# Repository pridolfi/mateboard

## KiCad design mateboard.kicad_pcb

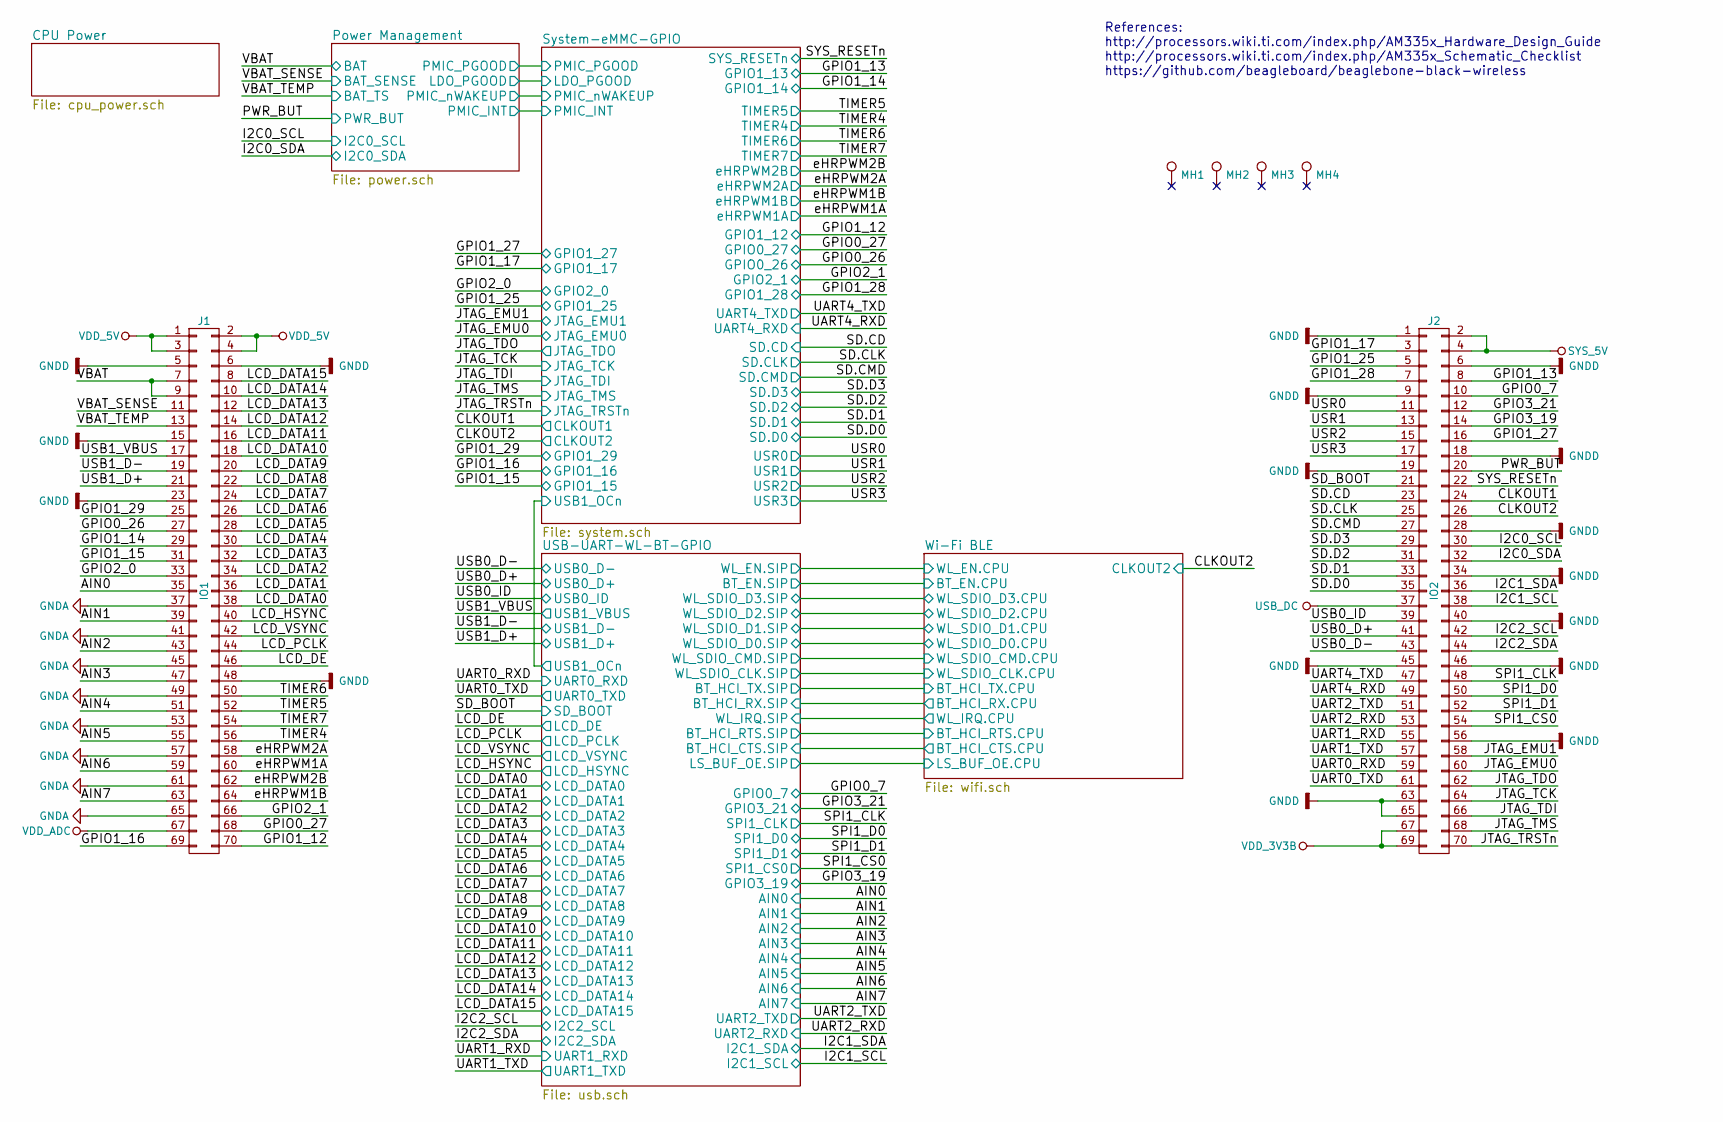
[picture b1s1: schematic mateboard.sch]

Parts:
J1: IO1; DF40C-70DP-0.4V_51_
J2: IO2; DF40C-70DP-0.4V_51_
MH1, MH2, MH3, MH4: Mounting hole; MountingHole_3.2mm_M3

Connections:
/AIN0: J1.35; also elsewhere on the board
/AIN1: J1.39; also elsewhere on the board
/AIN2: J1.43; also elsewhere on the board
/AIN3: J1.47; also elsewhere on the board
/AIN4: J1.51; also elsewhere on the board
/AIN5: J1.55; also elsewhere on the board
/AIN6: J1.59; also elsewhere on the board
/AIN7: J1.63; also elsewhere on the board
/CLKOUT1: J2.24; also elsewhere on the board
/CLKOUT2: J2.26; also elsewhere on the board
/GPIO0_7: J2.10; also elsewhere on the board
/GPIO0_26: J1.27; also elsewhere on the board
/GPIO0_27: J1.68; also elsewhere on the board
/GPIO1_12: J1.70; also elsewhere on the board
/GPIO1_13: J2.8; also elsewhere on the board
/GPIO1_14: J1.29; also elsewhere on the board
/GPIO1_15: J1.31; also elsewhere on the board
/GPIO1_16: J1.69; also elsewhere on the board
/GPIO1_17: J2.3; also elsewhere on the board
/GPIO1_25: J2.5; also elsewhere on the board
/GPIO1_27: J2.16; also elsewhere on the board
/GPIO1_28: J2.7; also elsewhere on the board
/GPIO1_29: J1.25; also elsewhere on the board
/GPIO2_0: J1.33; also elsewhere on the board
/GPIO2_1: J1.66; also elsewhere on the board
/GPIO3_19: J2.14; also elsewhere on the board
/GPIO3_21: J2.12; also elsewhere on the board
/I2C0_SCL: J2.30; also elsewhere on the board
/I2C0_SDA: J2.32; also elsewhere on the board
/I2C1_SCL: J2.38; also elsewhere on the board
/I2C1_SDA: J2.36; also elsewhere on the board
/I2C2_SCL: J2.42; also elsewhere on the board
/I2C2_SDA: J2.44; also elsewhere on the board
/JTAG_EMU0: J2.60; also elsewhere on the board
/JTAG_EMU1: J2.58; also elsewhere on the board
/JTAG_TCK: J2.64; also elsewhere on the board
/JTAG_TDI: J2.66; also elsewhere on the board
/JTAG_TDO: J2.62; also elsewhere on the board
/JTAG_TMS: J2.68; also elsewhere on the board
/JTAG_TRSTn: J2.70; also elsewhere on the board
/LCD_DATA0: J1.38; also elsewhere on the board
/LCD_DATA1: J1.36; also elsewhere on the board
/LCD_DATA2: J1.34; also elsewhere on the board
/LCD_DATA3: J1.32; also elsewhere on the board
/LCD_DATA4: J1.30; also elsewhere on the board
/LCD_DATA5: J1.28; also elsewhere on the board
/LCD_DATA6: J1.26; also elsewhere on the board
/LCD_DATA7: J1.24; also elsewhere on the board
/LCD_DATA8: J1.22; also elsewhere on the board
/LCD_DATA9: J1.20; also elsewhere on the board
/LCD_DATA10: J1.18; also elsewhere on the board
/LCD_DATA11: J1.16; also elsewhere on the board
/LCD_DATA12: J1.14; also elsewhere on the board
/LCD_DATA13: J1.12; also elsewhere on the board
/LCD_DATA14: J1.10; also elsewhere on the board
/LCD_DATA15: J1.8; also elsewhere on the board
/LCD_DE: J1.46; also elsewhere on the board
/LCD_HSYNC: J1.40; also elsewhere on the board
/LCD_PCLK: J1.44; also elsewhere on the board
/LCD_VSYNC: J1.42; also elsewhere on the board
/PWR_BUT: J2.20; also elsewhere on the board
/SD.CD: J2.23; also elsewhere on the board
/SD.CLK: J2.25; also elsewhere on the board
/SD.CMD: J2.27; also elsewhere on the board
/SD.D0: J2.35; also elsewhere on the board
/SD.D1: J2.33; also elsewhere on the board
/SD.D2: J2.31; also elsewhere on the board
/SD.D3: J2.29; also elsewhere on the board
/SD_BOOT: J2.21; also elsewhere on the board
/SPI1_CLK: J2.48; also elsewhere on the board
/SPI1_CS0: J2.54; also elsewhere on the board
/SPI1_D0: J2.50; also elsewhere on the board
/SPI1_D1: J2.52; also elsewhere on the board
/SYS_RESETn: J2.22; also elsewhere on the board
/TIMER4: J1.56; also elsewhere on the board
/TIMER5: J1.52; also elsewhere on the board
/TIMER6: J1.50; also elsewhere on the board
/TIMER7: J1.54; also elsewhere on the board
/UART0_RXD: J2.59; also elsewhere on the board
/UART0_TXD: J2.61; also elsewhere on the board
/UART1_RXD: J2.55; also elsewhere on the board
/UART1_TXD: J2.57; also elsewhere on the board
/UART2_RXD: J2.53; also elsewhere on the board
/UART2_TXD: J2.51; also elsewhere on the board
/UART4_RXD: J2.49; also elsewhere on the board
/UART4_TXD: J2.47; also elsewhere on the board
/USB0_D+: J2.41; also elsewhere on the board
/USB0_D-: J2.43; also elsewhere on the board
/USB0_ID: J2.39; also elsewhere on the board
/USB1_D+: J1.21; also elsewhere on the board
/USB1_D-: J1.19; also elsewhere on the board
/USB1_VBUS: J1.17; also elsewhere on the board
/USR0: J2.11; also elsewhere on the board
/USR1: J2.13; also elsewhere on the board
/USR2: J2.15; also elsewhere on the board
/USR3: J2.17; also elsewhere on the board
/VBAT: J1.7, J1.9; also elsewhere on the board
/VBAT_SENSE: J1.11; also elsewhere on the board
/VBAT_TEMP: J1.13; also elsewhere on the board
/eHRPWM1A: J1.60; also elsewhere on the board
/eHRPWM1B: J1.64; also elsewhere on the board
/eHRPWM2A: J1.58; also elsewhere on the board
/eHRPWM2B: J1.62; also elsewhere on the board
GNDA: J1.37, J1.41, J1.45, J1.49, J1.53, J1.57, J1.61, J1.65; also elsewhere on the board
GNDD: J1.5, J1.6, J1.15, J1.23, J1.48, J2.1, J2.6, J2.9, J2.18, J2.19, J2.28, J2.34, J2.40, J2.45, J2.46, J2.56, J2.63, J2.65; also elsewhere on the board
SYS_5V: J2.2, J2.4; also elsewhere on the board
USB_DC: J2.37; also elsewhere on the board
VDD_3V3B: J2.67, J2.69; also elsewhere on the board
VDD_5V: J1.1, J1.2, J1.3, J1.4; also elsewhere on the board
VDD_ADC: J1.67; also elsewhere on the board

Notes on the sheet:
References: http://processors.wiki.ti.com/index.php/AM335x_Hardware_Design_Guide http://processors.wiki.ti.com/index.php/AM335x_Schematic_Checklist https://github.com/beagleboard/beaglebone-black-wireless

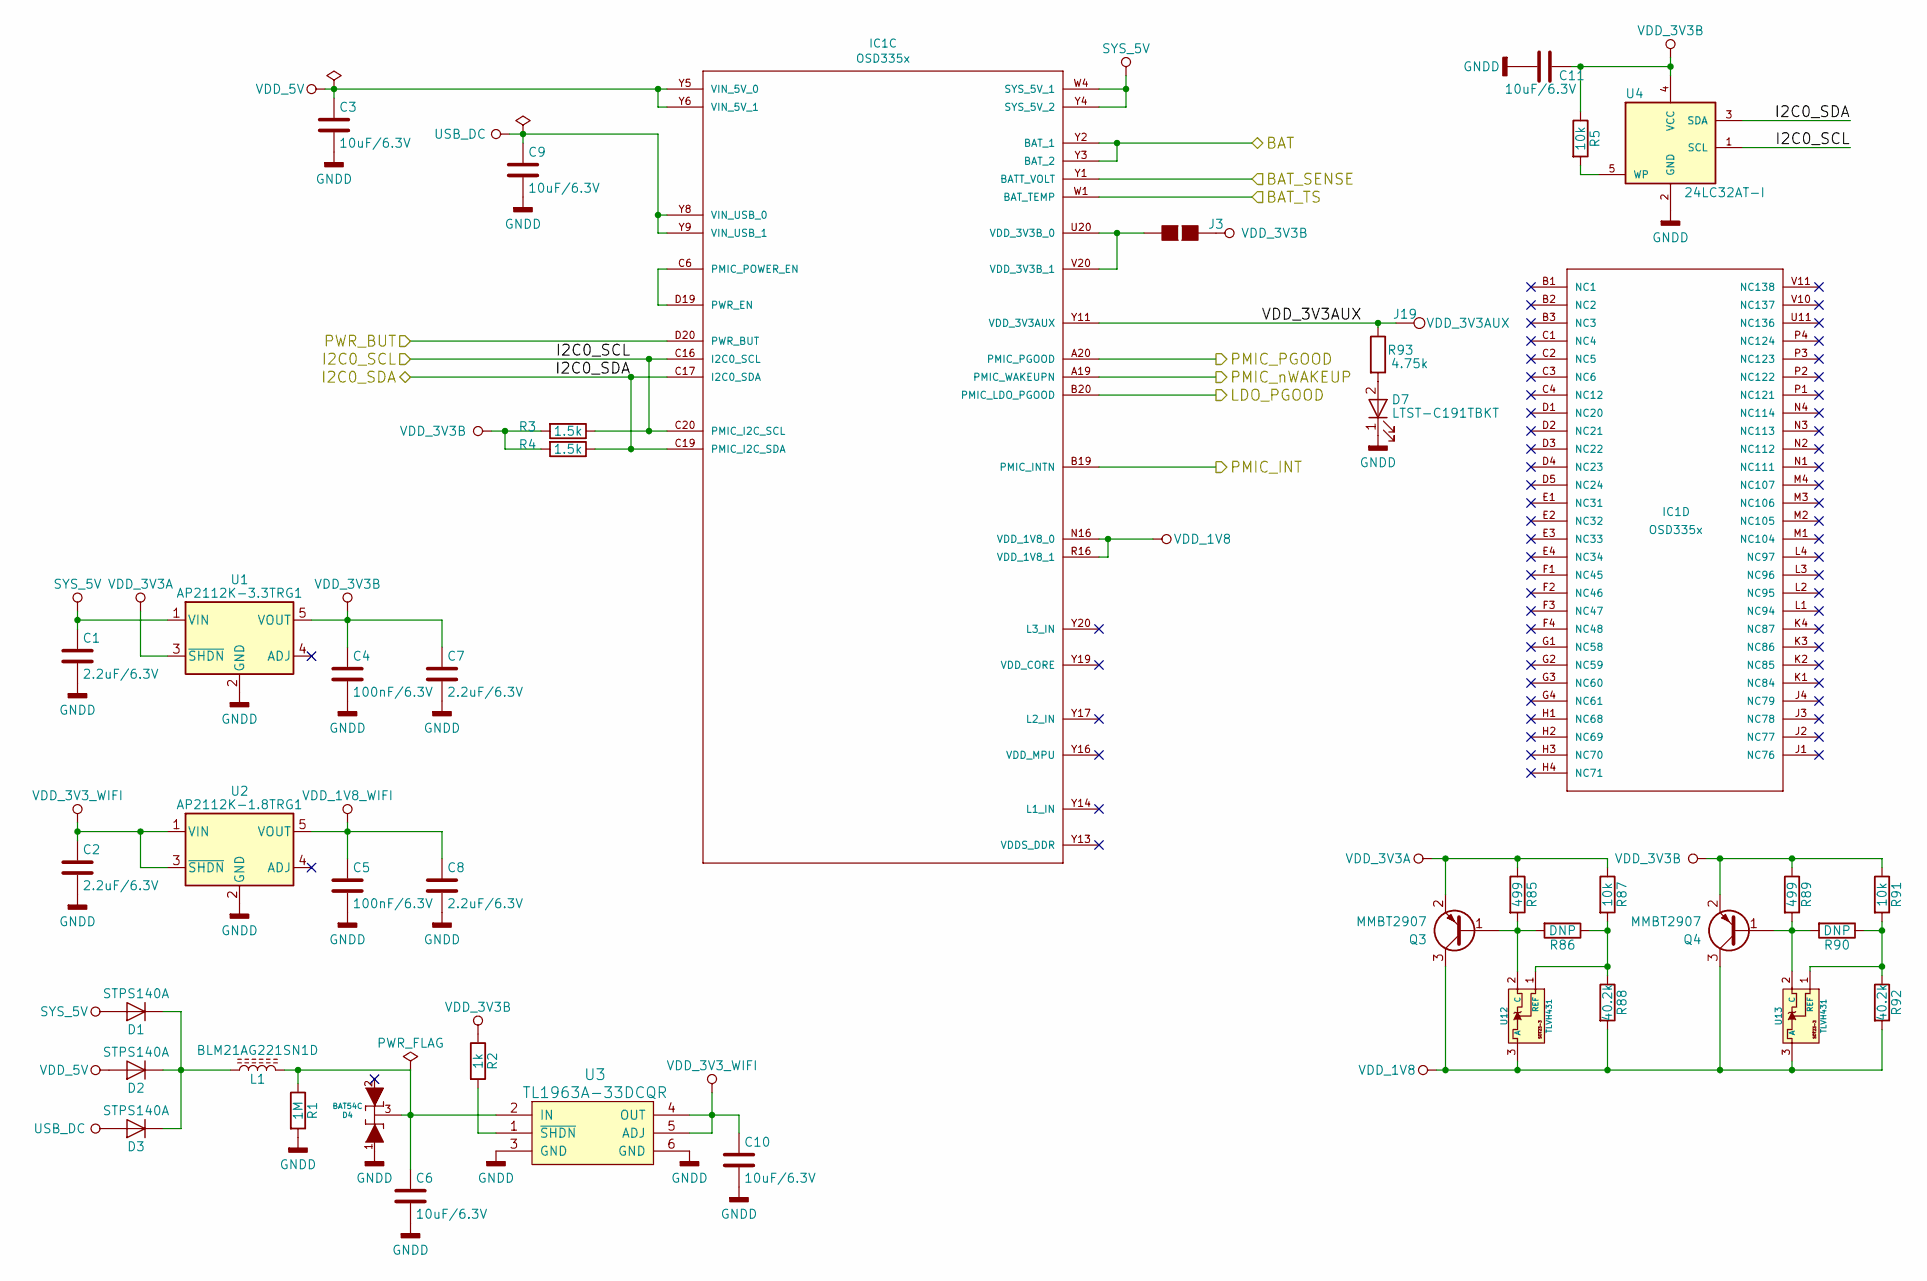
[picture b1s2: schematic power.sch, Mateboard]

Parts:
C1, C2, C7, C8: 2.2uF/6.3V; C_0603
C3, C6, C9, C10, C11: 10uF/6.3V; C_0603
C4, C5: 100nF/6.3V; C_0402
D1, D2, D3: STPS140A; D_SMA_Standard
D4: BAT54C; SOT-23
D7: LTST-C191TBKT; LED_0603
IC1: OSD335x; OSD3358-BAS-BGA400
J3: GS2
J19: VDD_3V3AUX; Measurement_Point_Round-SMD-Pad_Small
L1: BLM21AG221SN1D; R_0805
Q3, Q4: MMBT2907; SOT-23
R1: 1M; R_0402
R2: 1k; R_0402
R3, R4: 1.5k; R_0402
R5, R87, R91: 10k; R_0402
R85, R89: 499; R_0402
R86, R90: DNP; R_0402
R88, R92: 40.2k; R_0402
R93: 4.75k; R_0402
U1: AP2112K-3.3TRG1; TSOT-23-5
U2: AP2112K-1.8TRG1; TSOT-23-5
U3: TL1963A-33DCQR; SOT-223-6
U4: 24LC32AT-I; SOT-23-5
U12, U13: TLVH431; SOT-23

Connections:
/I2C0_SCL: IC1.C16 (I2C0_SCL), IC1.C20 (PMIC_I2C_SCL), R3.1, U4.1 (SCL); also elsewhere on the board
/I2C0_SDA: IC1.C17 (I2C0_SDA), IC1.C19 (PMIC_I2C_SDA), R4.1, U4.3 (SDA); also elsewhere on the board
/PWR_BUT: IC1.D20 (PWR_BUT); also elsewhere on the board
/Power Management/LDO_PGOOD: IC1.B20 (PMIC_LDO_PGOOD); also elsewhere on the board
/Power Management/PMIC_INT: IC1.B19 (PMIC_INTN); also elsewhere on the board
/Power Management/PMIC_PGOOD: IC1.A20 (PMIC_PGOOD); also elsewhere on the board
/Power Management/PMIC_nWAKEUP: IC1.A19 (PMIC_WAKEUPN); also elsewhere on the board
/Power Management/VDD_3V3AUX: IC1.Y11 (VDD_3V3AUX), J19.1, R93.1
/VBAT: IC1.Y2 (BAT_1), IC1.Y3 (BAT_2); also elsewhere on the board
/VBAT_SENSE: IC1.Y1 (BATT_VOLT); also elsewhere on the board
/VBAT_TEMP: IC1.W1 (BAT_TEMP); also elsewhere on the board
GNDD: C1.2, C2.2, C3.2, C4.2, C5.2, C6.2, C7.2, C8.2, C9.2, C10.2, C11.2, D4.1 (B), D7.1 (K), R1.2, U1.2 (GND), U2.2 (GND), U3.3 (GND), U3.6 (GND), U4.2 (GND); also elsewhere on the board
unnamed: C6.1, D4.3 (C), L1.2, R1.1, U3.2 (IN)
unnamed: D1.1 (K), D2.1 (K), D3.1 (K), L1.1
unnamed: D7.2 (A), R93.2
unnamed: IC1.C6 (PMIC_POWER_EN), IC1.D19 (PWR_EN)
unnamed: IC1.U20 (VDD_3V3B_0), IC1.V20 (VDD_3V3B_1), J3.2 (G2)
unnamed: Q3.1 (B), R85.2, R86.2, U12.2 (C)
unnamed: Q4.1 (B), R89.2, R90.2, U13.2 (C)
unnamed: R2.2, U3.1 (~SHDN)
unnamed: R5.2, U4.5 (WP)
unnamed: R86.1, R87.2, R88.1, U12.1 (REF)
unnamed: R90.1, R91.2, R92.1, U13.1 (REF)
SYS_5V: C1.1, D1.2 (A), IC1.W4 (SYS_5V_1), IC1.Y4 (SYS_5V_2), U1.1 (VIN); also elsewhere on the board
USB_DC: C9.1, D3.2 (A), IC1.Y8 (VIN_USB_0), IC1.Y9 (VIN_USB_1); also elsewhere on the board
VDD_1V8: IC1.N16 (VDD_1V8_0), IC1.R16 (VDD_1V8_1), Q3.3 (C), Q4.3 (C), R88.2, R92.2, U12.3 (A), U13.3 (A); also elsewhere on the board
VDD_1V8_WIFI: C5.1, C8.1, U2.5 (VOUT); also elsewhere on the board
VDD_3V3A: Q3.2 (E), R85.1, R87.1, U1.3 (~SHDN); also elsewhere on the board
VDD_3V3B: C4.1, C7.1, C11.1, J3.1 (G1), Q4.2 (E), R2.1, R3.2, R4.2, R5.1, R89.1, R91.1, U1.5 (VOUT), U4.4 (VCC); also elsewhere on the board
VDD_3V3_WIFI: C2.1, C10.1, U2.1 (VIN), U2.3 (~SHDN), U3.4 (OUT), U3.5 (ADJ); also elsewhere on the board
VDD_5V: C3.1, D2.2 (A), IC1.Y5 (VIN_5V_0), IC1.Y6 (VIN_5V_1); also elsewhere on the board

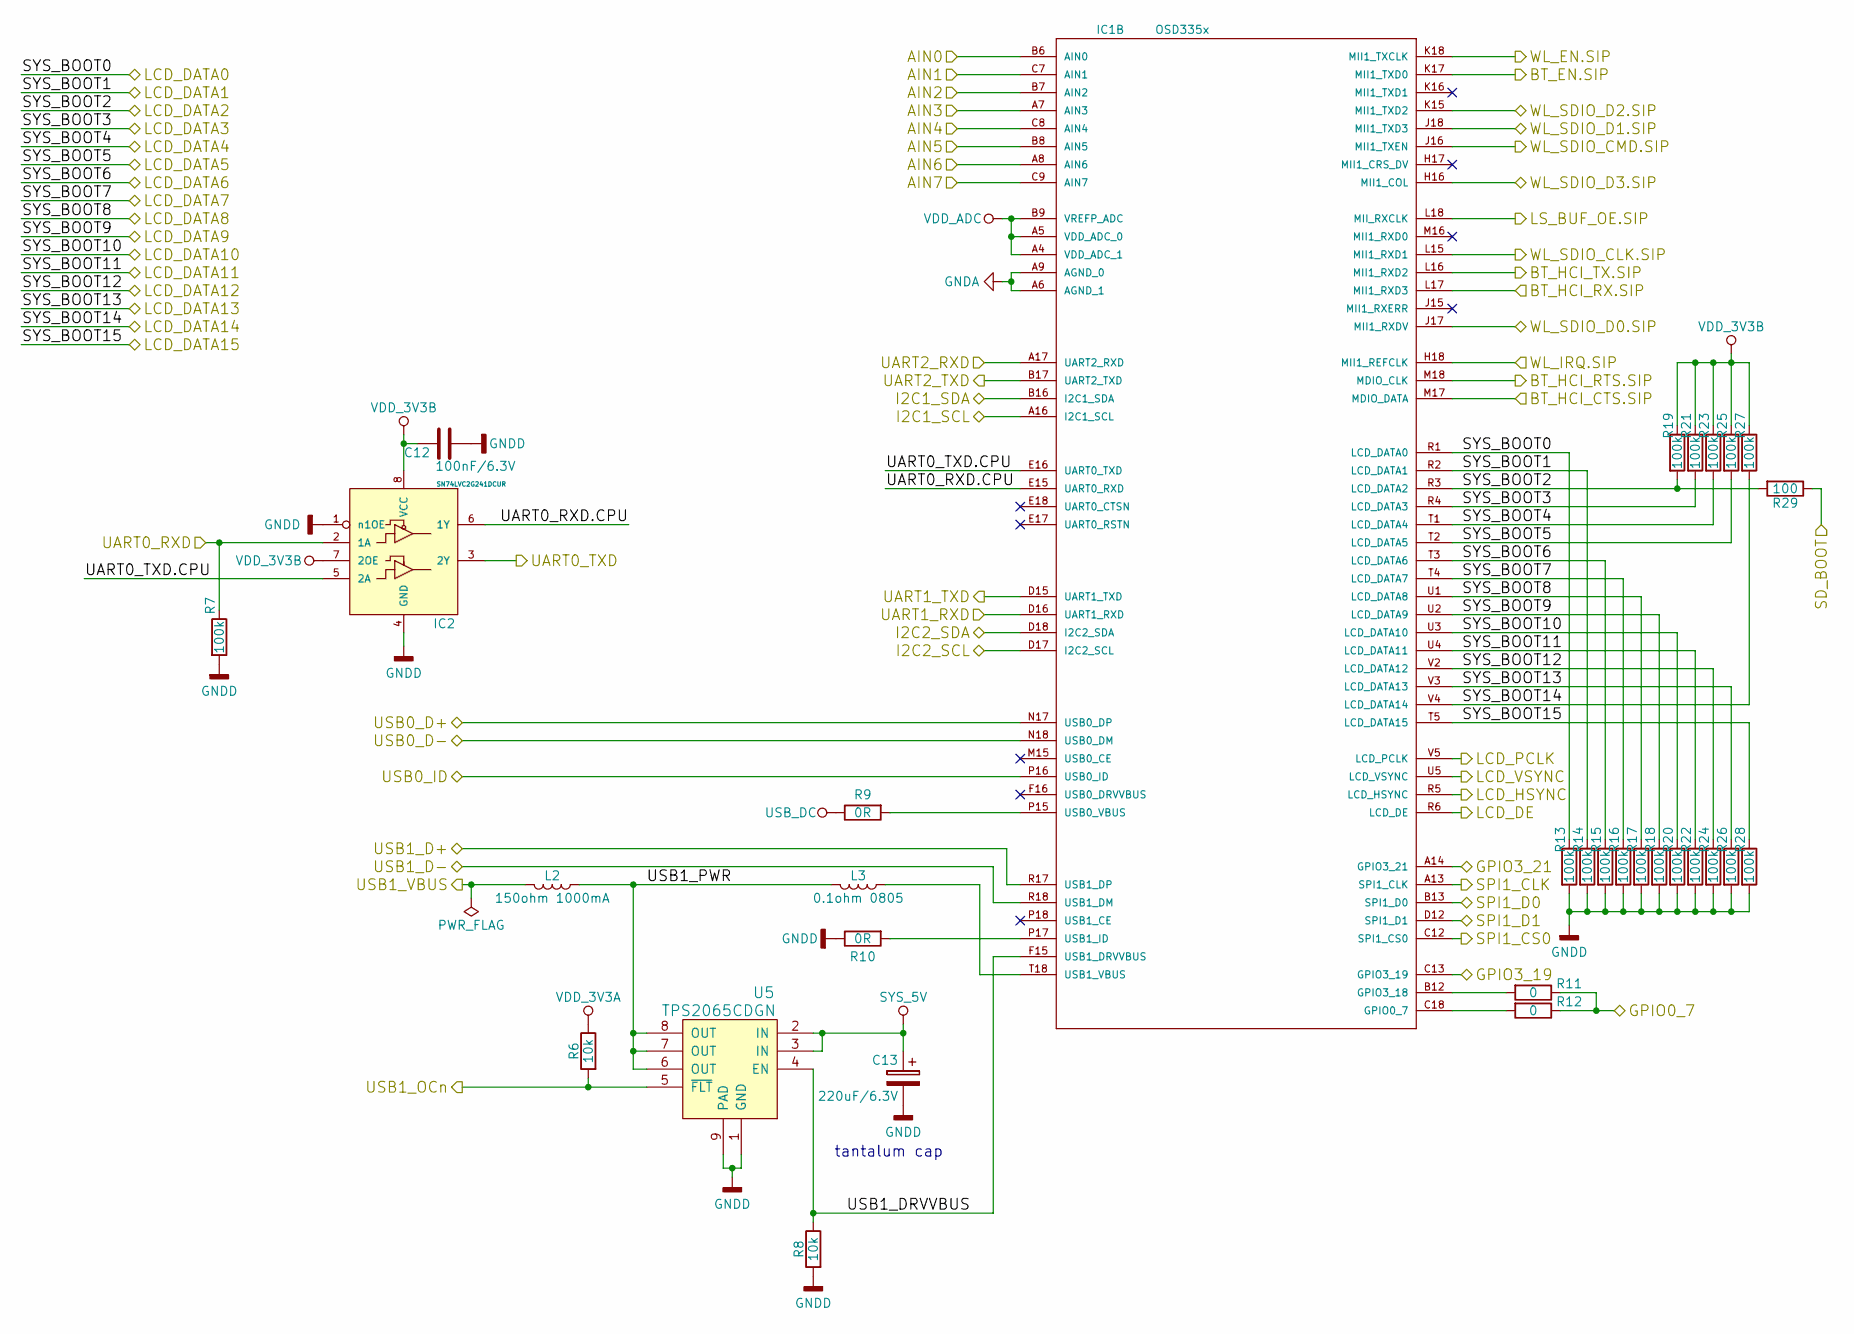
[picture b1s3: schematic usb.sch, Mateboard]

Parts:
C12: 100nF/6.3V; C_0402
C13: 220uF/6.3V; CP_Tantalum_Case-A_EIA-3216-18_Reflow
IC1: OSD335x; OSD3358-BAS-BGA400
IC2: SN74LVC2G241DCUR; VSSOP-8_2.3x2mm_Pitch0.5mm
L2: 150ohm 1000mA; R_0805
L3: 0.1ohm 0805; R_0805
R6, R8: 10k; R_0402
R7, R13, R14, R15, R16, R17, R18, R19, R20, R21, R22, R23, R24, R25, R26, R27, R28: 100k; R_0402
R9, R10: 0R; R_0402
R11, R12: 0; R_0402
R29: 100; R_0402
U5: TPS2065CDGN; MSOP-8-1EP_3x3mm_Pitch0.65mm

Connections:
/AIN0: IC1.B6 (AIN0); also elsewhere on the board
/AIN1: IC1.C7 (AIN1); also elsewhere on the board
/AIN2: IC1.B7 (AIN2); also elsewhere on the board
/AIN3: IC1.A7 (AIN3); also elsewhere on the board
/AIN4: IC1.C8 (AIN4); also elsewhere on the board
/AIN5: IC1.B8 (AIN5); also elsewhere on the board
/AIN6: IC1.A8 (AIN6); also elsewhere on the board
/AIN7: IC1.C9 (AIN7); also elsewhere on the board
/GPIO0_7: R11.1, R12.1; also elsewhere on the board
/GPIO3_19: IC1.C13 (GPIO3_19); also elsewhere on the board
/GPIO3_21: IC1.A14 (GPIO3_21); also elsewhere on the board
/I2C1_SCL: IC1.A16 (I2C1_SCL); also elsewhere on the board
/I2C1_SDA: IC1.B16 (I2C1_SDA); also elsewhere on the board
/I2C2_SCL: IC1.D17 (I2C2_SCL); also elsewhere on the board
/I2C2_SDA: IC1.D18 (I2C2_SDA); also elsewhere on the board
/LCD_DATA0: IC1.R1 (LCD_DATA0), R13.1; also elsewhere on the board
/LCD_DATA1: IC1.R2 (LCD_DATA1), R14.1; also elsewhere on the board
/LCD_DATA2: IC1.R3 (LCD_DATA2), R19.2, R29.2; also elsewhere on the board
/LCD_DATA3: IC1.R4 (LCD_DATA3), R21.2; also elsewhere on the board
/LCD_DATA4: IC1.T1 (LCD_DATA4), R23.2; also elsewhere on the board
/LCD_DATA5: IC1.T2 (LCD_DATA5), R25.2; also elsewhere on the board
/LCD_DATA6: IC1.T3 (LCD_DATA6), R15.1; also elsewhere on the board
/LCD_DATA7: IC1.T4 (LCD_DATA7), R16.1; also elsewhere on the board
/LCD_DATA8: IC1.U1 (LCD_DATA8), R17.1; also elsewhere on the board
/LCD_DATA9: IC1.U2 (LCD_DATA9), R18.1; also elsewhere on the board
/LCD_DATA10: IC1.U3 (LCD_DATA10), R20.1; also elsewhere on the board
/LCD_DATA11: IC1.U4 (LCD_DATA11), R22.1; also elsewhere on the board
/LCD_DATA12: IC1.V2 (LCD_DATA12), R24.1; also elsewhere on the board
/LCD_DATA13: IC1.V3 (LCD_DATA13), R26.1; also elsewhere on the board
/LCD_DATA14: IC1.V4 (LCD_DATA14), R27.2; also elsewhere on the board
/LCD_DATA15: IC1.T5 (LCD_DATA15), R28.1; also elsewhere on the board
/LCD_DE: IC1.R6 (LCD_DE); also elsewhere on the board
/LCD_HSYNC: IC1.R5 (LCD_HSYNC); also elsewhere on the board
/LCD_PCLK: IC1.V5 (LCD_PCLK); also elsewhere on the board
/LCD_VSYNC: IC1.U5 (LCD_VSYNC); also elsewhere on the board
/SD_BOOT: R29.1; also elsewhere on the board
/SPI1_CLK: IC1.A13 (SPI1_CLK); also elsewhere on the board
/SPI1_CS0: IC1.C12 (SPI1_CS0); also elsewhere on the board
/SPI1_D0: IC1.B13 (SPI1_D0); also elsewhere on the board
/SPI1_D1: IC1.D12 (SPI1_D1); also elsewhere on the board
/System-eMMC-GPIO/USB1_OCn: R6.2, U5.5 (~FLT); also elsewhere on the board
/UART0_RXD: IC2.2 (1A), R7.1; also elsewhere on the board
/UART0_TXD: IC2.3 (2Y); also elsewhere on the board
/UART1_RXD: IC1.D16 (UART1_RXD); also elsewhere on the board
/UART1_TXD: IC1.D15 (UART1_TXD); also elsewhere on the board
/UART2_RXD: IC1.A17 (UART2_RXD); also elsewhere on the board
/UART2_TXD: IC1.B17 (UART2_TXD); also elsewhere on the board
/USB0_D+: IC1.N17 (USB0_DP); also elsewhere on the board
/USB0_D-: IC1.N18 (USB0_DM); also elsewhere on the board
/USB0_ID: IC1.P16 (USB0_ID); also elsewhere on the board
/USB1_D+: IC1.R17 (USB1_DP); also elsewhere on the board
/USB1_D-: IC1.R18 (USB1_DM); also elsewhere on the board
/USB1_VBUS: L2.1; also elsewhere on the board
/USB-UART-WL-BT-GPIO/UART0_RXD.CPU: IC1.E15 (UART0_RXD), IC2.6 (1Y)
/USB-UART-WL-BT-GPIO/UART0_TXD.CPU: IC1.E16 (UART0_TXD), IC2.5 (2A)
/USB-UART-WL-BT-GPIO/USB1_DRVVBUS: IC1.F15 (USB1_DRVVBUS), R8.1, U5.4 (EN)
/USB-UART-WL-BT-GPIO/USB1_PWR: L2.2, L3.1, U5.6 (OUT), U5.7 (OUT), U5.8 (OUT)
/Wi-Fi BLE/BT_EN.CPU: IC1.K17 (MII1_TXD0); also elsewhere on the board
/Wi-Fi BLE/BT_HCI_CTS.CPU: IC1.M17 (MDIO_DATA); also elsewhere on the board
/Wi-Fi BLE/BT_HCI_RTS.CPU: IC1.M18 (MDIO_CLK); also elsewhere on the board
/Wi-Fi BLE/BT_HCI_RX.CPU: IC1.L17 (MII1_RXD3); also elsewhere on the board
/Wi-Fi BLE/BT_HCI_TX.CPU: IC1.L16 (MII1_RXD2); also elsewhere on the board
/Wi-Fi BLE/LS_BUF_OE.CPU: IC1.L18 (MII_RXCLK); also elsewhere on the board
/Wi-Fi BLE/WL_EN.CPU: IC1.K18 (MII1_TXCLK); also elsewhere on the board
/Wi-Fi BLE/WL_IRQ.CPU: IC1.H18 (MII1_REFCLK); also elsewhere on the board
/Wi-Fi BLE/WL_SDIO_CLK.CPU: IC1.L15 (MII1_RXD1); also elsewhere on the board
/Wi-Fi BLE/WL_SDIO_CMD.CPU: IC1.J16 (MII1_TXEN); also elsewhere on the board
/Wi-Fi BLE/WL_SDIO_D0.CPU: IC1.J17 (MII1_RXDV); also elsewhere on the board
/Wi-Fi BLE/WL_SDIO_D1.CPU: IC1.J18 (MII1_TXD3); also elsewhere on the board
/Wi-Fi BLE/WL_SDIO_D2.CPU: IC1.K15 (MII1_TXD2); also elsewhere on the board
/Wi-Fi BLE/WL_SDIO_D3.CPU: IC1.H16 (MII1_COL); also elsewhere on the board
GNDA: IC1.A6 (AGND_1), IC1.A9 (AGND_0); also elsewhere on the board
GNDD: C12.2, C13.2, IC2.1 (n1OE), IC2.4 (GND), R7.2, R8.2, R10.1, R13.2, R14.2, R15.2, R16.2, R17.2, R18.2, R20.2, R22.2, R24.2, R26.2, R28.2, U5.1 (GND), U5.9 (PAD); also elsewhere on the board
unnamed: IC1.B12 (GPIO3_18), R11.2
unnamed: IC1.C18 (GPIO0_7), R12.2
unnamed: IC1.P15 (USB0_VBUS), R9.2
unnamed: IC1.P17 (USB1_ID), R10.2
unnamed: IC1.T18 (USB1_VBUS), L3.2
SYS_5V: C13.1, U5.2 (IN), U5.3 (IN); also elsewhere on the board
USB_DC: R9.1; also elsewhere on the board
VDD_3V3A: R6.1; also elsewhere on the board
VDD_3V3B: C12.1, IC2.7 (2OE), IC2.8 (VCC), R19.1, R21.1, R23.1, R25.1, R27.1; also elsewhere on the board
VDD_ADC: IC1.A4 (VDD_ADC_1), IC1.A5 (VDD_ADC_0), IC1.B9 (VREFP_ADC); also elsewhere on the board

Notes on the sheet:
tantalum cap

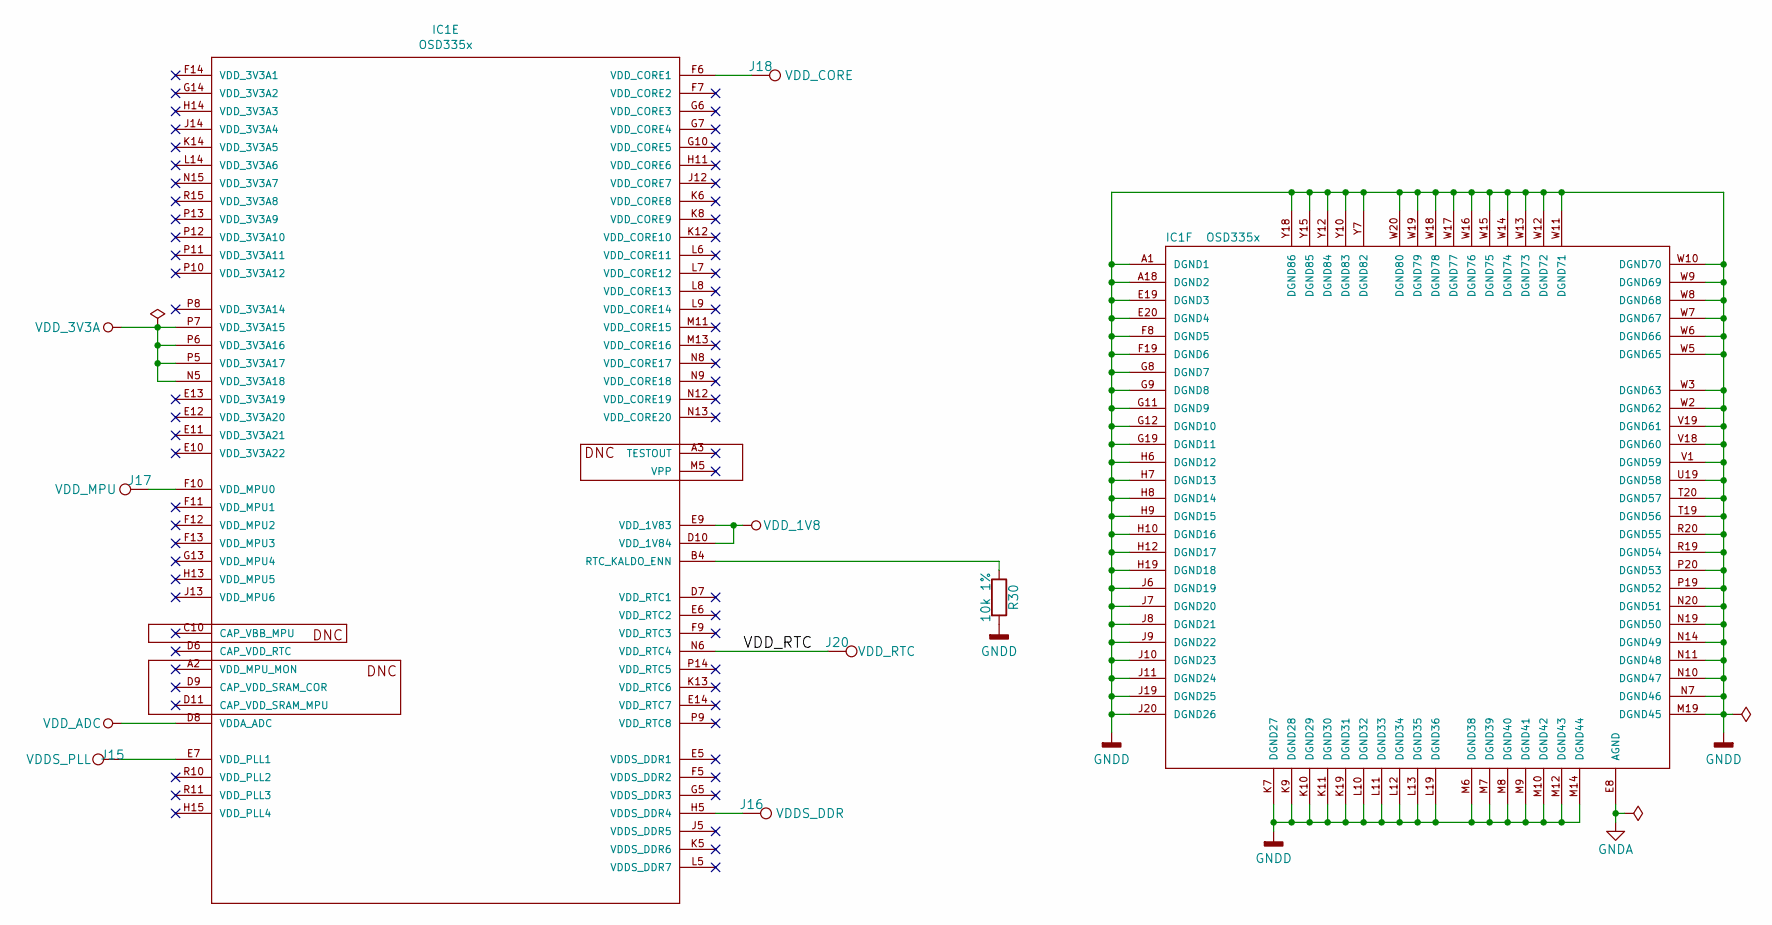
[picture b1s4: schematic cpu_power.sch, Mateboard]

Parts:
IC1: OSD335x; OSD3358-BAS-BGA400
J15: VDDS_PLL; Measurement_Point_Round-SMD-Pad_Small
J16: VDDS_DDR; Measurement_Point_Round-SMD-Pad_Small
J17: VDD_MPU; Measurement_Point_Round-SMD-Pad_Small
J18: VDD_CORE; Measurement_Point_Round-SMD-Pad_Small
J20: VDD_RTC; Measurement_Point_Round-SMD-Pad_Small
R30: 10k 1%; R_0402

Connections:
/CPU Power/VDD_RTC: IC1.N6 (VDD_RTC4), J20.1
GNDA: IC1.E8 (AGND); also elsewhere on the board
GNDD: IC1.A1 (DGND1), IC1.A18 (DGND2), IC1.E19 (DGND3), IC1.E20 (DGND4), IC1.F8 (DGND5), IC1.F19 (DGND6), IC1.G8 (DGND7), IC1.G9 (DGND8), IC1.G11 (DGND9), IC1.G12 (DGND10), IC1.G19 (DGND11), IC1.H6 (DGND12), IC1.H7 (DGND13), IC1.H8 (DGND14), IC1.H9 (DGND15), IC1.H10 (DGND16), IC1.H12 (DGND17), IC1.H19 (DGND18), IC1.J6 (DGND19), IC1.J7 (DGND20), IC1.J8 (DGND21), IC1.J9 (DGND22), IC1.J10 (DGND23), IC1.J11 (DGND24), IC1.J19 (DGND25), IC1.J20 (DGND26), IC1.K7 (DGND27), IC1.K9 (DGND28), IC1.K10 (DGND29), IC1.K11 (DGND30), IC1.K19 (DGND31), IC1.L10 (DGND32), IC1.L11 (DGND33), IC1.L12 (DGND34), IC1.L13 (DGND35), IC1.L19 (DGND36), IC1.M6 (DGND38), IC1.M7 (DGND39), IC1.M8 (DGND40), IC1.M9 (DGND41), IC1.M10 (DGND42), IC1.M12 (DGND43), IC1.M14 (DGND44), IC1.M19 (DGND45), IC1.N7 (DGND46), IC1.N10 (DGND47), IC1.N11 (DGND48), IC1.N14 (DGND49), IC1.N19 (DGND50), IC1.N20 (DGND51), IC1.P19 (DGND52), IC1.P20 (DGND53), IC1.R19 (DGND54), IC1.R20 (DGND55), IC1.T19 (DGND56), IC1.T20 (DGND57), IC1.U19 (DGND58), IC1.V1 (DGND59), IC1.V18 (DGND60), IC1.V19 (DGND61), IC1.W2 (DGND62), IC1.W3 (DGND63), IC1.W5 (DGND65), IC1.W6 (DGND66), IC1.W7 (DGND67), IC1.W8 (DGND68), IC1.W9 (DGND69), IC1.W10 (DGND70), IC1.W11 (DGND71), IC1.W12 (DGND72), IC1.W13 (DGND73), IC1.W14 (DGND74), IC1.W15 (DGND75), IC1.W16 (DGND76), IC1.W17 (DGND77), IC1.W18 (DGND78), IC1.W19 (DGND79), IC1.W20 (DGND80), IC1.Y7 (DGND82), IC1.Y10 (DGND83), IC1.Y12 (DGND84), IC1.Y15 (DGND85), IC1.Y18 (DGND86), R30.2; also elsewhere on the board
unnamed: IC1.B4 (RTC_KALDO_ENN), R30.1
unnamed: IC1.E7 (VDD_PLL1), J15.1
unnamed: IC1.F6 (VDD_CORE1), J18.1
unnamed: IC1.F10 (VDD_MPU0), J17.1
unnamed: IC1.H5 (VDDS_DDR4), J16.1
VDD_1V8: IC1.D10 (VDD_1V84), IC1.E9 (VDD_1V83); also elsewhere on the board
VDD_3V3A: IC1.N5 (VDD_3V3A18), IC1.P5 (VDD_3V3A17), IC1.P6 (VDD_3V3A16), IC1.P7 (VDD_3V3A15); also elsewhere on the board
VDD_ADC: IC1.D8 (VDDA_ADC); also elsewhere on the board
